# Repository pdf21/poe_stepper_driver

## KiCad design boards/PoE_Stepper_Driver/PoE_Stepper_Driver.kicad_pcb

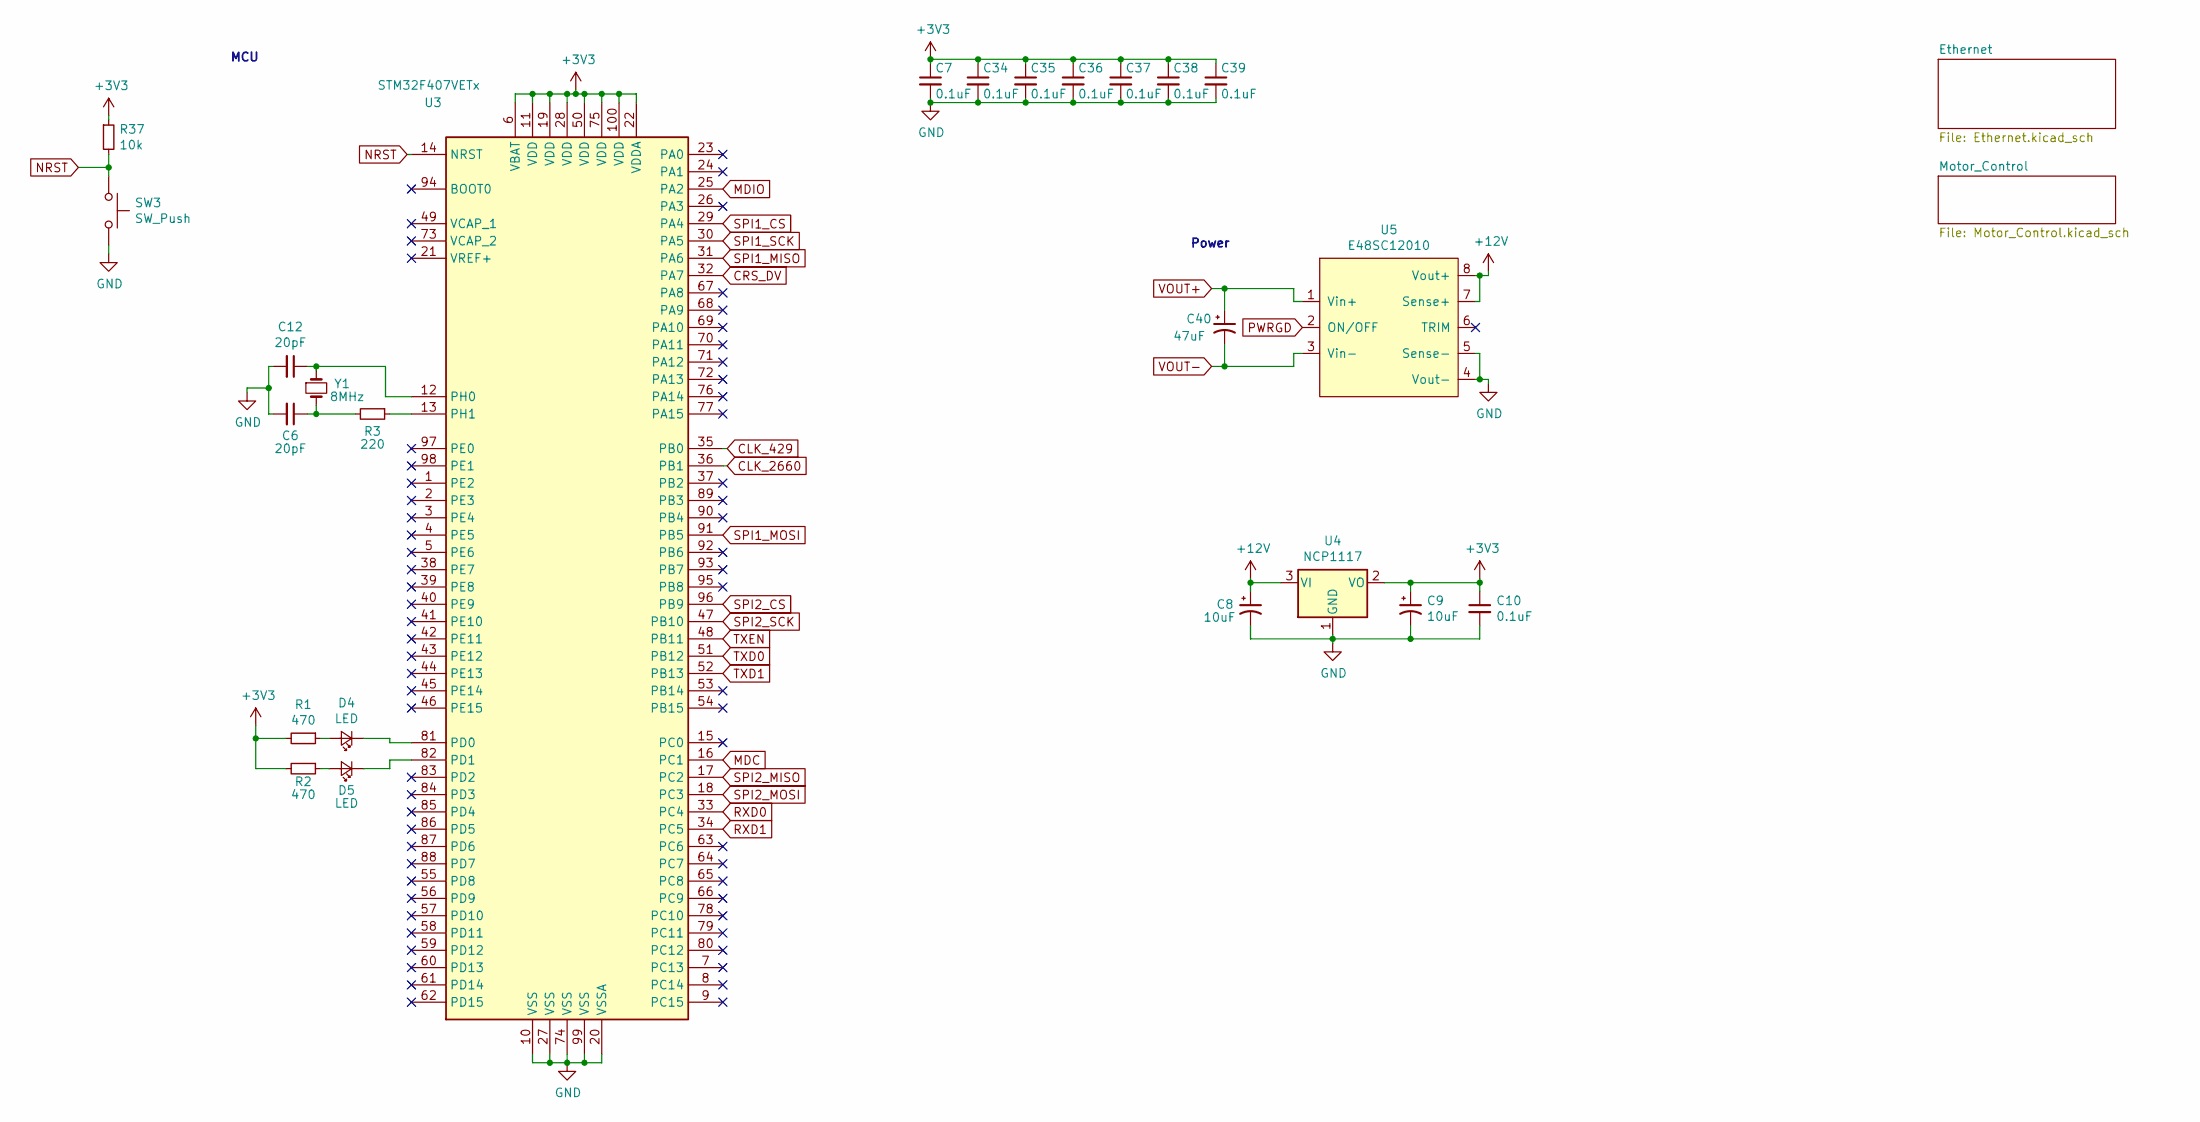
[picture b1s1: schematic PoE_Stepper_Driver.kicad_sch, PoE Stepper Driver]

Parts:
C6, C12: 20pF; C_0603_1608Metric_Pad1.05x0.95mm_HandSolder
C7, C10, C34, C35, C36, C37, C38, C39: 0.1uF; C_0805_2012Metric_Pad1.15x1.40mm_HandSolder
C8, C9: 10uF; CP_Elec_6.3x5.4
C40: 47uF; CP_Radial_D8.0mm_P3.50mm
D4, D5: LED; LED_0805_2012Metric_Pad1.15x1.40mm_HandSolder
R1, R2: 470; R_0805_2012Metric_Pad1.15x1.40mm_HandSolder
R3: 220; R_0603_1608Metric_Pad1.05x0.95mm_HandSolder
R37: 10k; R_0805_2012Metric_Pad1.15x1.40mm_HandSolder
SW3: SW_Push; SW_SPST_B3S-1000
U3: STM32F407VETx; LQFP-100_14x14mm_P0.5mm
U4: NCP1117; SOT-223-3_TabPin2
U5: E48SC12010
Y1: 8MHz; Crystal_HC49-4H_Vertical

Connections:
+3V3: C7.1, C9.1, C10.1, C34.1, C35.1, C36.1, C37.1, C38.1, C39.1, R1.2, R2.2, R37.1, U3.6 (VBAT), U3.11 (VDD), U3.19 (VDD), U3.22 (VDDA), U3.28 (VDD), U3.50 (VDD), U3.75 (VDD), U3.100 (VDD), U4.2 (VO); also elsewhere on the board
+12V: C8.1, U4.3 (VI), U5.7 (Sense+), U5.8 (Vout+); also elsewhere on the board
CLK_429: U3.35 (PB0); also elsewhere on the board
CLK_2660: U3.36 (PB1); also elsewhere on the board
CRS_DV: U3.32 (PA7); also elsewhere on the board
GND: C6.2, C7.2, C8.2, C9.2, C10.2, C12.2, C34.2, C35.2, C36.2, C37.2, C38.2, C39.2, SW3.2, U3.10 (VSS), U3.20 (VSSA), U3.27 (VSS), U3.74 (VSS), U3.99 (VSS), U4.1 (GND), U5.4 (Vout-), U5.5 (Sense-); also elsewhere on the board
MDC: U3.16 (PC1); also elsewhere on the board
MDIO: U3.25 (PA2); also elsewhere on the board
NRST: R37.2, SW3.1, U3.14 (NRST); also elsewhere on the board
unnamed: C6.1, R3.2, Y1.2
unnamed: C12.1, U3.12 (PH0), Y1.1
unnamed: D4.1 (K), U3.81 (PD0)
unnamed: D4.2 (A), R1.1
unnamed: D5.1 (K), U3.82 (PD1)
unnamed: D5.2 (A), R2.1
unnamed: R3.1, U3.13 (PH1)
PWRGD: U5.2 (ON/OFF); also elsewhere on the board
RXD0: U3.33 (PC4); also elsewhere on the board
RXD1: U3.34 (PC5); also elsewhere on the board
SPI1_CS: U3.29 (PA4); also elsewhere on the board
SPI1_MISO: U3.31 (PA6); also elsewhere on the board
SPI1_MOSI: U3.91 (PB5); also elsewhere on the board
SPI1_SCK: U3.30 (PA5); also elsewhere on the board
SPI2_CS: U3.96 (PB9); also elsewhere on the board
SPI2_MISO: U3.17 (PC2); also elsewhere on the board
SPI2_MOSI: U3.18 (PC3); also elsewhere on the board
SPI2_SCK: U3.47 (PB10); also elsewhere on the board
TXD0: U3.51 (PB12); also elsewhere on the board
TXD1: U3.52 (PB13); also elsewhere on the board
TXEN: U3.48 (PB11); also elsewhere on the board
VOUT+: C40.1, U5.1 (Vin+); also elsewhere on the board
VOUT-: C40.2, U5.3 (Vin-); also elsewhere on the board

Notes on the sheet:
Power
MCU

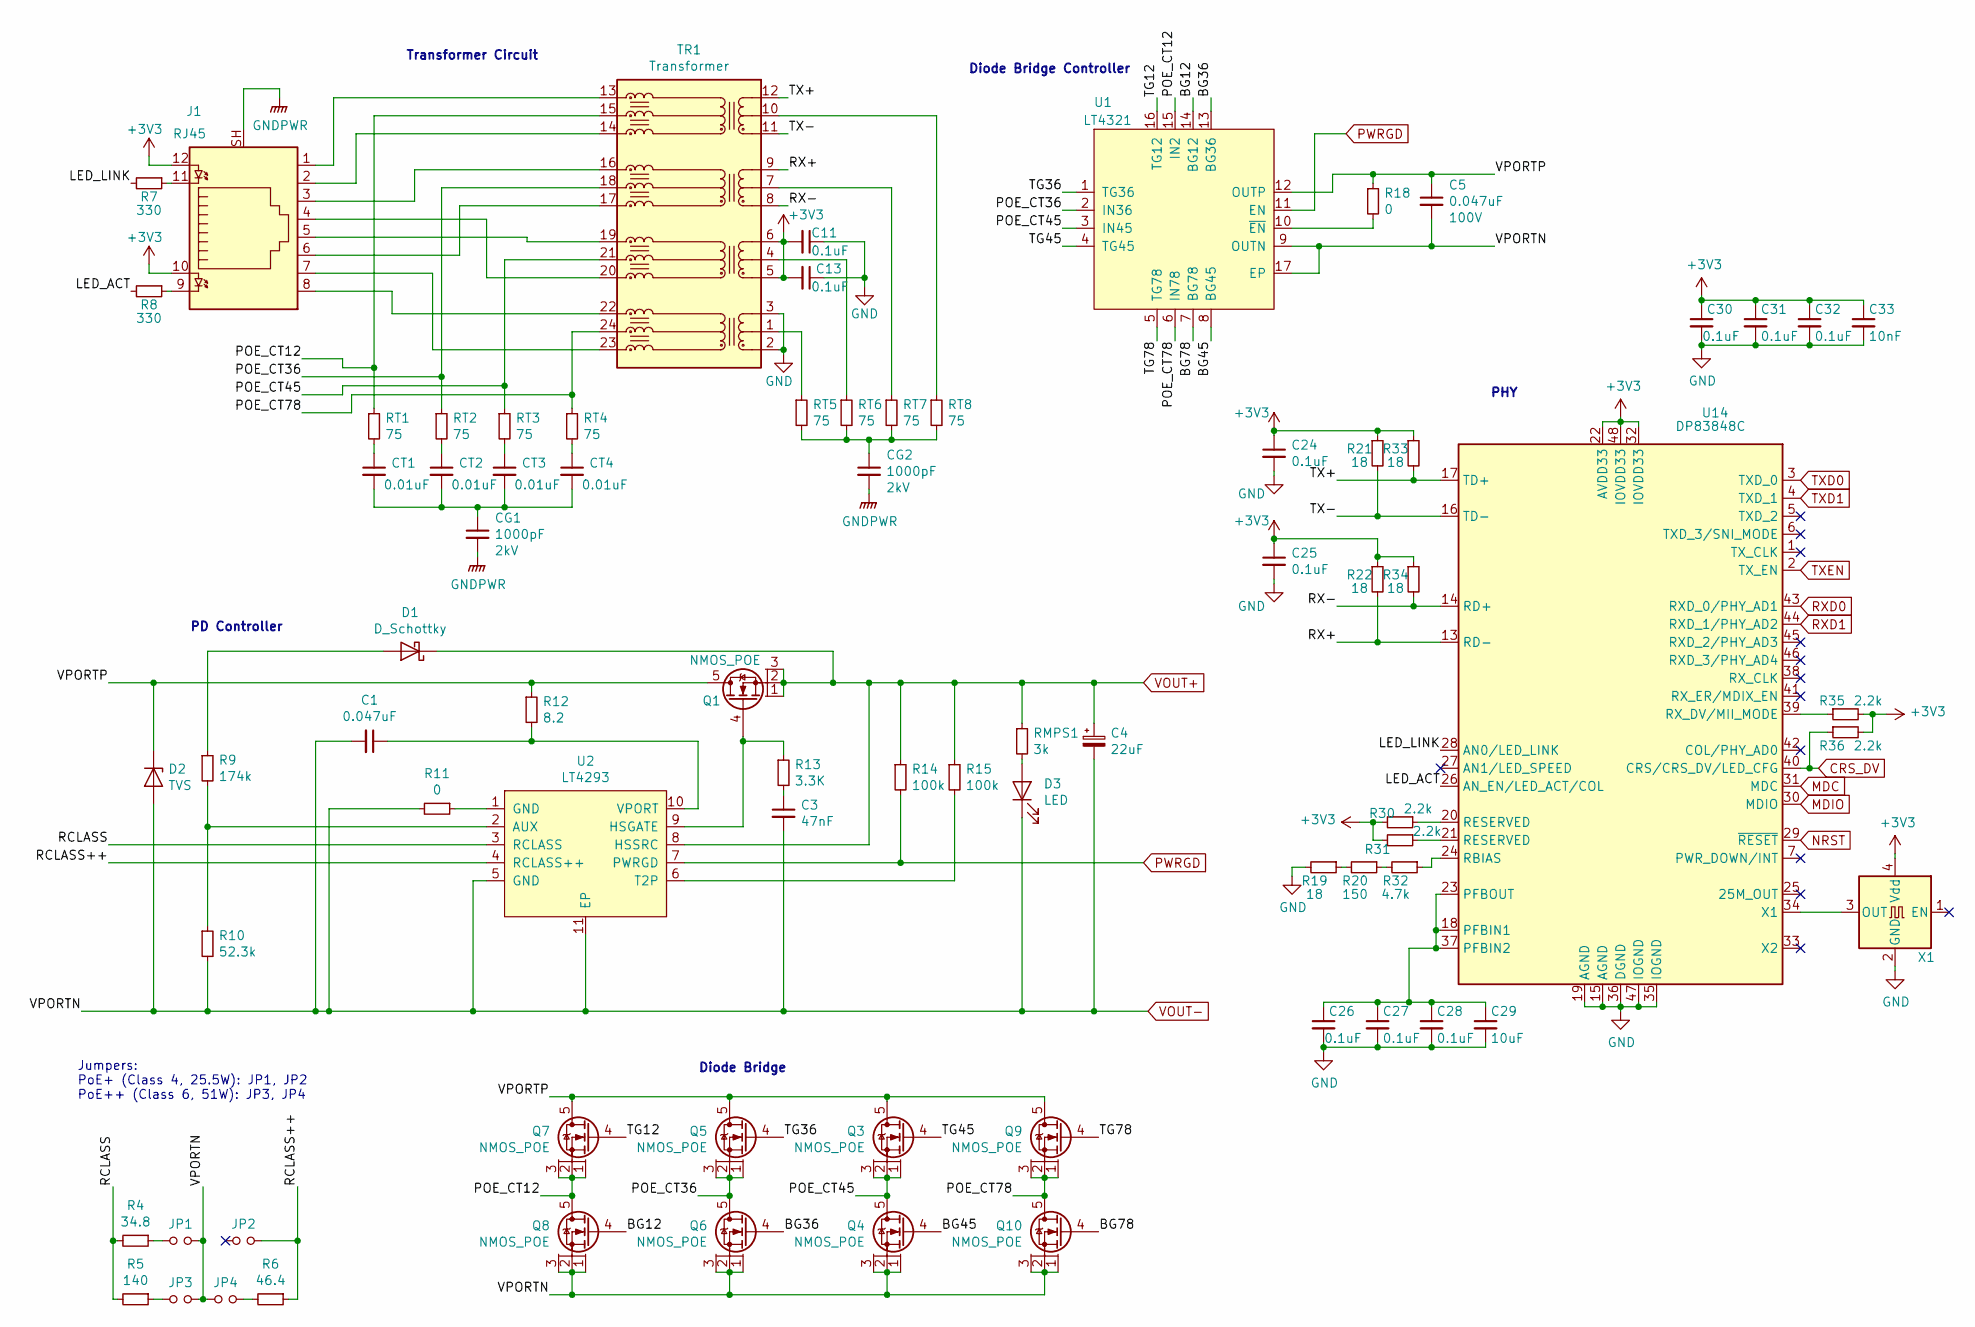
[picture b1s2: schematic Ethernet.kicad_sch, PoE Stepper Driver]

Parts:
C1: 0.047uF; C_0603_1608Metric_Pad1.05x0.95mm_HandSolder
C3: 47nF; C_0805_2012Metric_Pad1.15x1.40mm_HandSolder
C4: 22uF; CP_Elec_8x10.5
C5: 0.047uF; C_0603_1608Metric_Pad1.05x0.95mm_HandSolder; Voltage 100V
C11, C13, C24, C25, C26, C27, C28, C30, C31, C32: 0.1uF; C_0805_2012Metric_Pad1.15x1.40mm_HandSolder
C29: 10uF; C_0805_2012Metric_Pad1.15x1.40mm_HandSolder
C33: 10nF; C_0805_2012Metric_Pad1.15x1.40mm_HandSolder
CG1, CG2: 1000pF; C_1812_4532Metric_Pad1.30x3.40mm_HandSolder; Voltage 2kV
CT1, CT2, CT3, CT4: 0.01uF; C_0805_2012Metric_Pad1.15x1.40mm_HandSolder
D1: D_Schottky; D_SOD-128
D2: TVS; D_SOD-128
D3: LED; LED_0805_2012Metric_Pad1.15x1.40mm_HandSolder
J1: RJ45; RJ45_Amphenol_RJMG1BD3B8K1ANR
JP1, JP2, JP3, JP4: Jumper_NO_Small; PinHeader_1x02_P2.54mm_Vertical
Q1, Q3, Q4, Q5, Q6, Q7, Q8, Q9, Q10: NMOS_POE; LFPAK33
R4: 34.8; R_0805_2012Metric_Pad1.15x1.40mm_HandSolder
R5: 140; R_0805_2012Metric_Pad1.15x1.40mm_HandSolder
R6: 46.4; R_0805_2012Metric_Pad1.15x1.40mm_HandSolder
R7, R8: 330; R_0805_2012Metric_Pad1.15x1.40mm_HandSolder
R9: 174k; R_0603_1608Metric_Pad1.05x0.95mm_HandSolder
R10: 52.3k; R_0603_1608Metric_Pad1.05x0.95mm_HandSolder
R11, R18: 0; R_0603_1608Metric_Pad1.05x0.95mm_HandSolder
R12: 8.2; R_0805_2012Metric_Pad1.15x1.40mm_HandSolder
R13: 3.3K; R_0603_1608Metric_Pad1.05x0.95mm_HandSolder
R14, R15: 100k; R_0603_1608Metric_Pad1.05x0.95mm_HandSolder
R19, R21, R22, R33, R34: 18; R_0805_2012Metric_Pad1.15x1.40mm_HandSolder
R20: 150; R_0805_2012Metric_Pad1.15x1.40mm_HandSolder
R30, R31, R35, R36: 2.2k; R_0805_2012Metric_Pad1.15x1.40mm_HandSolder
R32: 4.7k; R_0805_2012Metric_Pad1.15x1.40mm_HandSolder
RMPS1: 3k; R_2512_6332Metric_Pad1.52x3.35mm_HandSolder
RT1, RT2, RT3, RT4, RT5, RT6, RT7, RT8: 75; R_0603_1608Metric_Pad1.05x0.95mm_HandSolder
TR1: Transformer; PoE_Transformer
U1: LT4321; QFN-16-1EP_4x4mm_P0.65mm_EP2.15x2.15mm
U2: LT4293; MSOP-10_3x3mm_P0.5mm
U14: DP83848C; LQFP-48_7x7mm_P0.5mm
X1: SXO53C

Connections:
+3V3: C11.2, C13.2, C24.1, C25.1, C30.1, C31.1, C32.1, C33.1, J1.10, J1.12, R21.1, R22.1, R30.2, R31.2, R33.1, R34.1, R35.2, R36.2, TR1.5 (TD2+), TR1.6 (TD2-), U14.22 (AVDD33), U14.32 (IOVDD33), U14.48 (IOVDD33), X1.4 (Vdd); also elsewhere on the board
/Ethernet/BG12: Q8.4, U1.14 (BG12)
/Ethernet/BG36: Q6.4, U1.13 (BG36)
/Ethernet/BG45: Q4.4, U1.8 (BG45)
/Ethernet/BG78: Q10.4, U1.7 (BG78)
/Ethernet/LED_ACT: R8.2, U14.26 (AN_EN/LED_ACT/COL)
/Ethernet/LED_LINK: R7.2, U14.28 (AN0/LED_LINK)
/Ethernet/POE_CT12: Q7.1, Q7.2, Q7.3, Q8.5, RT1.1, TR1.15 (MCT4), U1.15 (IN2)
/Ethernet/POE_CT36: Q5.1, Q5.2, Q5.3, Q6.5, RT2.1, TR1.18 (MCT3), U1.2 (IN36)
/Ethernet/POE_CT45: Q3.1, Q3.2, Q3.3, Q4.5, RT3.1, TR1.21 (MCT2), U1.3 (IN45)
/Ethernet/POE_CT78: Q9.1, Q9.2, Q9.3, Q10.5, RT4.1, TR1.24 (MTC1), U1.6 (IN78)
/Ethernet/RCLASS: R4.2, R5.2, U2.3 (RCLASS)
/Ethernet/RCLASS++: JP2.2, R6.1, U2.4 (RCLASS++)
/Ethernet/RX+: R22.2, TR1.9 (TD3-), U14.13 (RD-)
/Ethernet/RX-: R34.2, TR1.8 (TD3+), U14.14 (RD+)
/Ethernet/TG12: Q7.4, U1.16 (TG12)
/Ethernet/TG36: Q5.4, U1.1 (TG36)
/Ethernet/TG45: Q3.4, U1.4 (TG45)
/Ethernet/TG78: Q9.4, U1.5 (TG78)
/Ethernet/TX+: R33.2, TR1.12 (TD4-), U14.17 (TD+)
/Ethernet/TX-: R21.2, TR1.11 (TD4+), U14.16 (TD-)
/Ethernet/VPORTP: C5.1, D2.1 (K), Q1.5, Q3.5, Q5.5, Q7.5, Q9.5, R12.1, R18.1, U1.12 (OUTP)
CRS_DV: R36.1, U14.40 (CRS/CRS_DV/LED_CFG); also elsewhere on the board
GND: C11.1, C13.1, C24.2, C25.2, C26.2, C27.2, C28.2, C29.2, C30.2, C31.2, C32.2, C33.2, R19.2, TR1.2 (TD1+), TR1.3 (TD1-), U14.15 (AGND), U14.19 (AGND), U14.35 (IOGND), U14.36 (DGND), U14.47 (IOGND), X1.2 (GND); also elsewhere on the board
GNDPWR: CG1.2, CG2.2, J1.SH
MDC: U14.31 (MDC); also elsewhere on the board
MDIO: U14.30 (MDIO); also elsewhere on the board
NRST: U14.29 (~RESET); also elsewhere on the board
unnamed: C1.1, R12.2, U2.10 (VPORT)
unnamed: C3.1, R13.2
unnamed: C26.1, C27.1, C28.1, C29.1, U14.18 (PFBIN1), U14.23 (PFBOUT), U14.37 (PFBIN2)
unnamed: CG1.1, CT1.2, CT2.2, CT3.2, CT4.2
unnamed: CG2.1, RT5.2, RT6.2, RT7.2, RT8.2
unnamed: CT1.1, RT1.2
unnamed: CT2.1, RT2.2
unnamed: CT3.1, RT3.2
unnamed: CT4.1, RT4.2
unnamed: D1.2 (A), R9.1
unnamed: D3.2 (A), RMPS1.2
unnamed: J1.1, TR1.13 (MX4-)
unnamed: J1.2, TR1.14 (MX4+)
unnamed: J1.3, TR1.16 (MTX3-)
unnamed: J1.4, TR1.20 (MTX2+)
unnamed: J1.5, TR1.19 (MTX2-)
unnamed: J1.6, TR1.17 (MTX3+)
unnamed: J1.7, TR1.23 (MTX1+)
unnamed: J1.8, TR1.22 (MTX1-)
unnamed: J1.9, R8.1
unnamed: J1.11, R7.1
unnamed: JP1.1, R4.1
unnamed: JP3.1, R5.1
unnamed: JP4.2, R6.2
unnamed: Q1.4, R13.1, U2.9 (HSGATE)
unnamed: R9.2, R10.1, U2.2 (AUX)
unnamed: R11.1, U2.1 (GND)
unnamed: R15.2, U2.6 (T2P)
unnamed: R18.2, U1.10 (~EN)
unnamed: R19.1, R20.2
unnamed: R20.1, R32.2
unnamed: R30.1, U14.20 (RESERVED)
unnamed: R31.1, U14.21 (RESERVED)
unnamed: R32.1, U14.24 (RBIAS)
unnamed: R35.1, U14.39 (RX_DV/MII_MODE)
unnamed: RT5.1, TR1.1 (TCT1)
unnamed: RT6.1, TR1.4 (TCT2)
unnamed: RT7.1, TR1.7 (TCT3)
unnamed: RT8.1, TR1.10 (TCT4)
unnamed: U14.34 (X1), X1.3 (OUT)
PWRGD: R14.2, U1.11 (EN), U2.7 (PWRGD); also elsewhere on the board
RXD0: U14.43 (RXD_0/PHY_AD1); also elsewhere on the board
RXD1: U14.44 (RXD_1/PHY_AD2); also elsewhere on the board
TXD0: U14.3 (TXD_0); also elsewhere on the board
TXD1: U14.4 (TXD_1); also elsewhere on the board
TXEN: U14.2 (TX_EN); also elsewhere on the board
VOUT+: C4.1, D1.1 (K), Q1.1, Q1.2, Q1.3, R14.1, R15.1, RMPS1.1, U2.8 (HSSRC); also elsewhere on the board
VOUT-: C1.2, C3.2, C4.2, C5.2, D2.2 (A), D3.1 (K), JP1.2, JP3.2, JP4.1, Q4.1, Q4.2, Q4.3, Q6.1, Q6.2, Q6.3, Q8.1, Q8.2, Q8.3, Q10.1, Q10.2, Q10.3, R10.2, R11.2, U1.9 (OUTN), U1.17 (EP), U2.5 (GND), U2.11 (EP); also elsewhere on the board

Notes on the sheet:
PD Controller
PHY
Diode Bridge
Transformer Circuit
Jumpers: PoE+ (Class 4, 25.5W): JP1, JP2 PoE++ (Class 6, 51W): JP3, JP4
Diode Bridge Controller

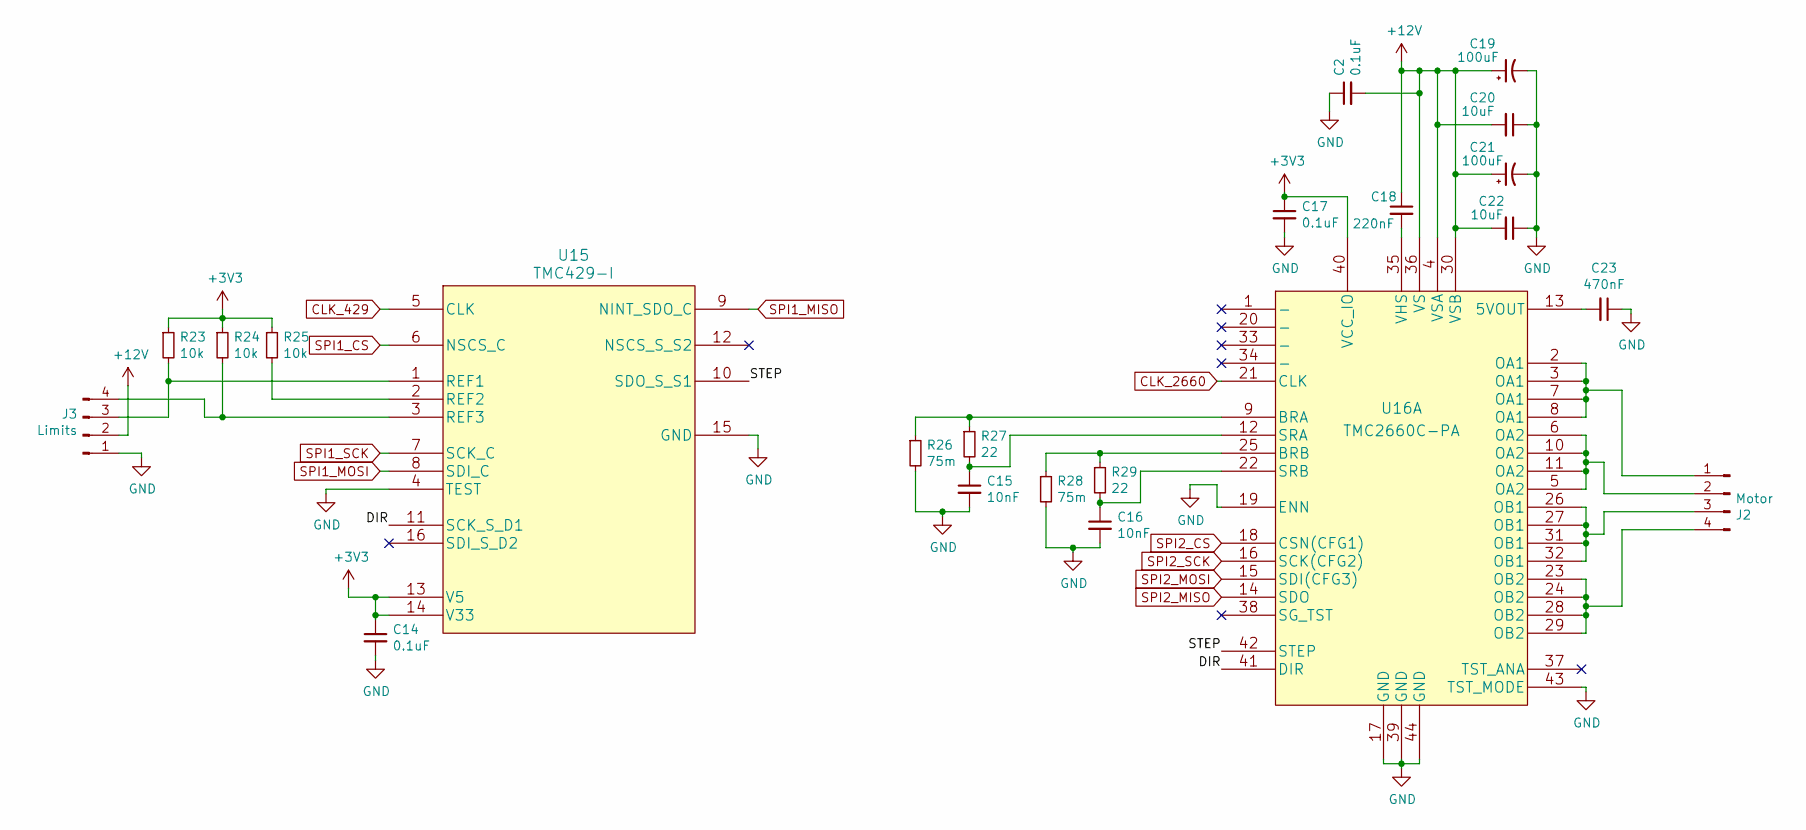
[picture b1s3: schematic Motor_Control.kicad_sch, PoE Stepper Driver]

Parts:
C2, C14, C17: 0.1uF; C_0805_2012Metric_Pad1.15x1.40mm_HandSolder
C15, C16: 10nF; C_0805_2012Metric_Pad1.15x1.40mm_HandSolder
C18: 220nF; C_0805_2012Metric_Pad1.15x1.40mm_HandSolder
C19, C21: 100uF; CP_Radial_D8.0mm_P3.50mm
C20, C22: 10uF; C_1206_3216Metric_Pad1.42x1.75mm_HandSolder
C23: 470nF; C_0805_2012Metric_Pad1.15x1.40mm_HandSolder
J2: Motor; JST_PH_B4B-PH-K_1x04_P2.00mm_Vertical
J3: Limits; JST_PH_B4B-PH-K_1x04_P2.00mm_Vertical
R23, R24, R25: 10k; R_0805_2012Metric_Pad1.15x1.40mm_HandSolder
R26, R28: 75m; R_2010_5025Metric_Pad1.52x2.65mm_HandSolder
R27, R29: 22; R_0805_2012Metric_Pad1.15x1.40mm_HandSolder
U15: TMC429-I; SSOP-16_3.9x4.9mm_P0.635mm
U16: TMC2660C-PA; PQFP-44_10x10mm_P0.8mm

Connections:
+3V3: C14.1, C17.1, R23.1, R24.1, R25.1, U15.13 (V5), U15.14 (V33), U16.40 (VCC_IO); also elsewhere on the board
+12V: C2.2, C18.1, C19.1, C20.2, C21.1, C22.2, J3.2, U16.4 (VSA), U16.30 (VSB), U16.36 (VS); also elsewhere on the board
/Motor_Control/DIR: U15.11 (SCK_S_D1), U16.41 (DIR)
/Motor_Control/STEP: U15.10 (SDO_S_S1), U16.42 (STEP)
CLK_429: U15.5 (CLK); also elsewhere on the board
CLK_2660: U16.21 (CLK); also elsewhere on the board
GND: C2.1, C14.2, C15.2, C16.2, C17.2, C19.2, C20.1, C21.2, C22.1, C23.1, J3.1, R26.2, R28.2, U15.4 (TEST), U15.15 (GND), U16.17 (GND), U16.19 (ENN), U16.39 (GND), U16.43 (TST_MODE), U16.44 (GND); also elsewhere on the board
unnamed: C15.1, R27.2, U16.12 (SRA)
unnamed: C16.1, R29.2, U16.22 (SRB)
unnamed: C18.2, U16.35 (VHS)
unnamed: C23.2, U16.13 (5VOUT)
unnamed: J2.1, U16.2 (OA1), U16.3 (OA1), U16.7 (OA1), U16.8 (OA1)
unnamed: J2.2, U16.5 (OA2), U16.6 (OA2), U16.10 (OA2), U16.11 (OA2)
unnamed: J2.3, U16.26 (OB1), U16.27 (OB1), U16.31 (OB1), U16.32 (OB1)
unnamed: J2.4, U16.23 (OB2), U16.24 (OB2), U16.28 (OB2), U16.29 (OB2)
unnamed: J3.3, R23.2, U15.1 (REF1)
unnamed: J3.4, R24.2, U15.3 (REF3)
unnamed: R25.2, U15.2 (REF2)
unnamed: R26.1, R27.1, U16.9 (BRA)
unnamed: R28.1, R29.1, U16.25 (BRB)
SPI1_CS: U15.6 (NSCS_C); also elsewhere on the board
SPI1_MISO: U15.9 (NINT_SDO_C); also elsewhere on the board
SPI1_MOSI: U15.8 (SDI_C); also elsewhere on the board
SPI1_SCK: U15.7 (SCK_C); also elsewhere on the board
SPI2_CS: U16.18 (CSN(CFG1)); also elsewhere on the board
SPI2_MISO: U16.14 (SDO); also elsewhere on the board
SPI2_MOSI: U16.15 (SDI(CFG3)); also elsewhere on the board
SPI2_SCK: U16.16 (SCK(CFG2)); also elsewhere on the board

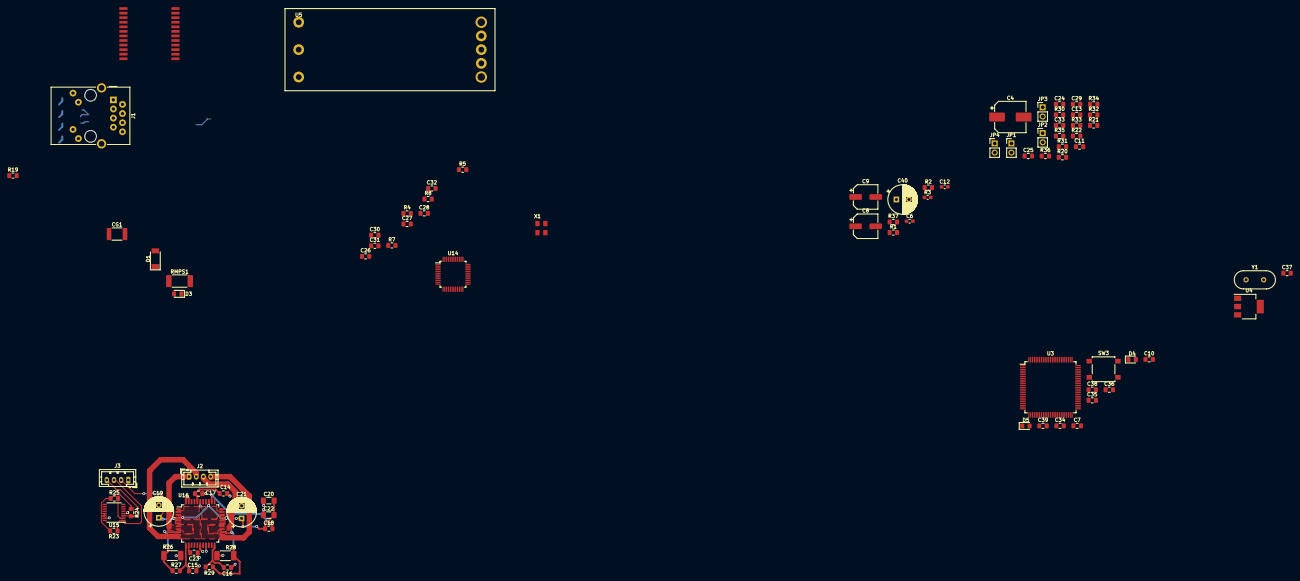
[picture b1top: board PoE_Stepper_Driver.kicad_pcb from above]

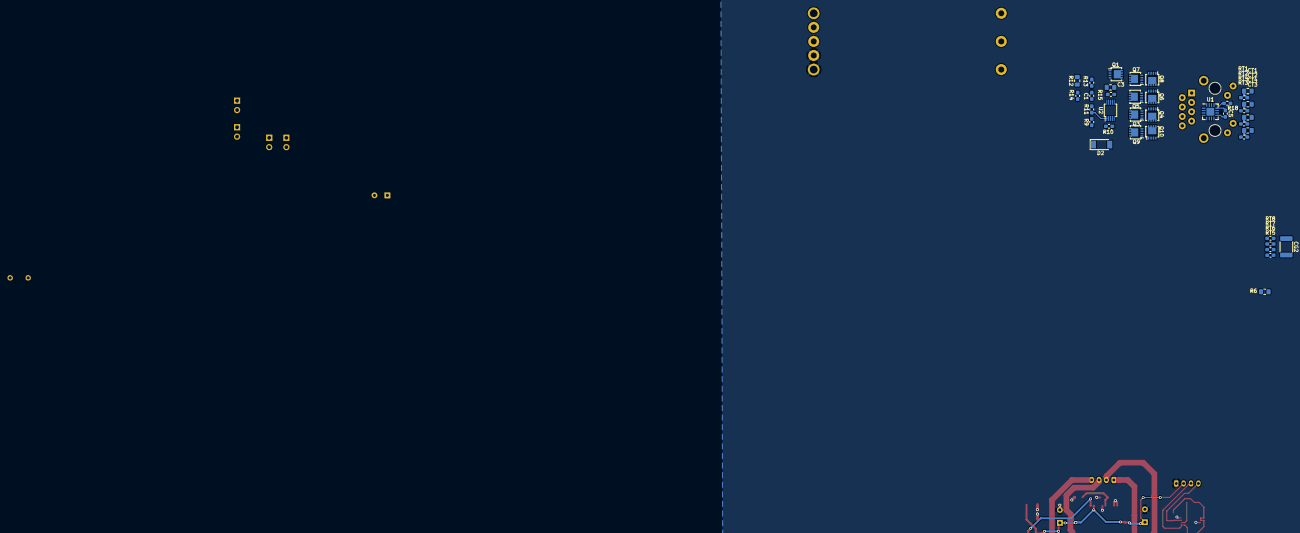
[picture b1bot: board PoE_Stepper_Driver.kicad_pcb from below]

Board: 2 copper layers, 122 parts (37 on the bottom side), 109 nets.

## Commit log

2022-03-03 1/2 of motor control
2022-03-04 motor control draft 1 done, remember to add capacitor C2 and be mindful of adding connection to power
